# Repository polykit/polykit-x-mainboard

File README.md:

# Polykit X8 Mainboard

_THIS IS NOT A FINISHED PRODUCT IN ANY WAY AND STILL UNDER HEAVY DEVELOPMENT - USE AT YOUR OWN RISK!_

This repository contains Kicad schematics and PCB layout for a main board for a polyphonic synthesizer that is controlled by a micro controller.

Key features:

* 8 voice cards
* 16-bit DAC
* Atmel2560 micro controller
* Eurorack powered
* MIDI input/output

All parameters of the voice cards are controlled by the DAC. That means patches can be stored and recalled.

There is a video playlist on the design process https://makertube.net/w/p/3N2fRjXwT2SfAUv2VkMy3e

Related repositories:

* Voice Card: https://github.com/polykit/polykit-x-voice-card
* Control Board: https://github.com/polykit/polykit-x-controlboard
* Input Board: _soon_
* Software: _soon_
* Power Supply: https://github.com/polykit/eurorack-psu

## BOM

|Reference                                                    |Value           |Footprint                                                     |Qty|
|-------------------------------------------------------------|----------------|--------------------------------------------------------------|---|
|C1, C2, C11-C18, C23-C25, C31-C34, C43-C47, C56-C59, C64, C65|100n ceramic    |Capacitor_SMD:C_1206_3216Metric_Pad1.33x1.80mm_HandSolder     |28 |
|C3-C10, C19-C22, C26-C29, C35-C42, C48-C55                   |10n film, PPS   |Capacitor_SMD:C_1206_3216Metric_Pad1.33x1.80mm_HandSolder     |32 |
|C30                                                          |10u             |Capacitor_SMD:CP_Elec_5x5.9                                   |1  |
|C60-C63                                                      |100u            |Capacitor_SMD:CP_Elec_6.3x7.7                                 |4  |
|D1                                                           |1N4148WS        |Diode_SMD:D_SOD-323_HandSoldering                             |1  |
|J1                                                           |POWER           |Connector_IDC:IDC-Header_2x08_P2.54mm_Vertical                |1  |
|J2                                                           |OUTPUT          |Connector_Molex:Molex_KK-254_AE-6410-03A_1x03_P2.54mm_Vertical|1  |
|J3                                                           |MIDI IN         |Connector_Molex:Molex_KK-254_AE-6410-02A_1x02_P2.54mm_Vertical|1  |
|J4                                                           |MIDI_OUT        |Connector_Molex:Molex_KK-254_AE-6410-02A_1x02_P2.54mm_Vertical|1  |
|J5                                                           |EXTERNAL_IN     |Connector_Molex:Molex_KK-254_AE-6410-02A_1x02_P2.54mm_Vertical|1  |
|J6                                                           |I2C_1           |Connector_IDC:IDC-Header_2x05_P2.54mm_Vertical                |1  |
|J7                                                           |I2C_2           |Connector_IDC:IDC-Header_2x05_P2.54mm_Vertical                |1  |
|J8                                                           |SPI             |Connector_IDC:IDC-Header_2x05_P2.54mm_Vertical                |1  |
|J9                                                           |EXT_ANALOG      |Connector_IDC:IDC-Header_2x08_P2.54mm_Vertical                |1  |
|J10                                                          |EXT_DIGITAL     |Connector_IDC:IDC-Header_2x05_P2.54mm_Vertical                |1  |
|R1-R7, R13-R41                                               |100k            |Resistor_SMD:R_1206_3216Metric_Pad1.30x1.75mm_HandSolder      |36 |
|R8, R42, R43                                                 |1k              |Resistor_SMD:R_1206_3216Metric_Pad1.30x1.75mm_HandSolder      |3  |
|R9-R12, R47                                                  |10k             |Resistor_SMD:R_1206_3216Metric_Pad1.30x1.75mm_HandSolder      |5  |
|R44-R46                                                      |220R            |Resistor_SMD:R_1206_3216Metric_Pad1.30x1.75mm_HandSolder      |3  |
|U1                                                           |Mega2560Pro_Mini|aga:Mega2560Pro_Embed_RobotDyn                                |1  |
|U2, U5, U12, U15                                             |CD4051B         |Package_SO:SO-16_5.3x10.2mm_P1.27mm                           |4  |
|U3, U4, U6-U8, U13, U14, U16, U17, U19                       |TL074           |Package_SO:SO-14_3.9x8.65mm_P1.27mm                           |10 |
|U9                                                           |LM4040AIM3-5.0  |Package_TO_SOT_SMD:SOT-23                                     |1  |
|U10                                                          |AD5676ARUZ      |Package_SO:TSSOP-20_4.4x6.5mm_P0.65mm                         |1  |
|U11                                                          |TL072           |Package_SO:SO-8_3.9x4.9mm_P1.27mm                             |1  |
|U18                                                          |L7905           |Package_TO_SOT_SMD:TO-263-2                                   |1  |
|U20                                                          |6N137           |Package_DIP:DIP-8_W7.62mm_SMDSocket_SmallPads                 |1  |
|VOICE1-VOICE8                                                |VOICE           |Connector_PinSocket_2.54mm:PinSocket_1x36_P2.54mm_Vertical    |8  |

## Tweaks

* If saw/triangle signal is not audible replace R38 with a 220k resistor on the voice cards

## References

https://www.analog.com/media/en/technical-documentation/data-sheets/ad5676.pdf

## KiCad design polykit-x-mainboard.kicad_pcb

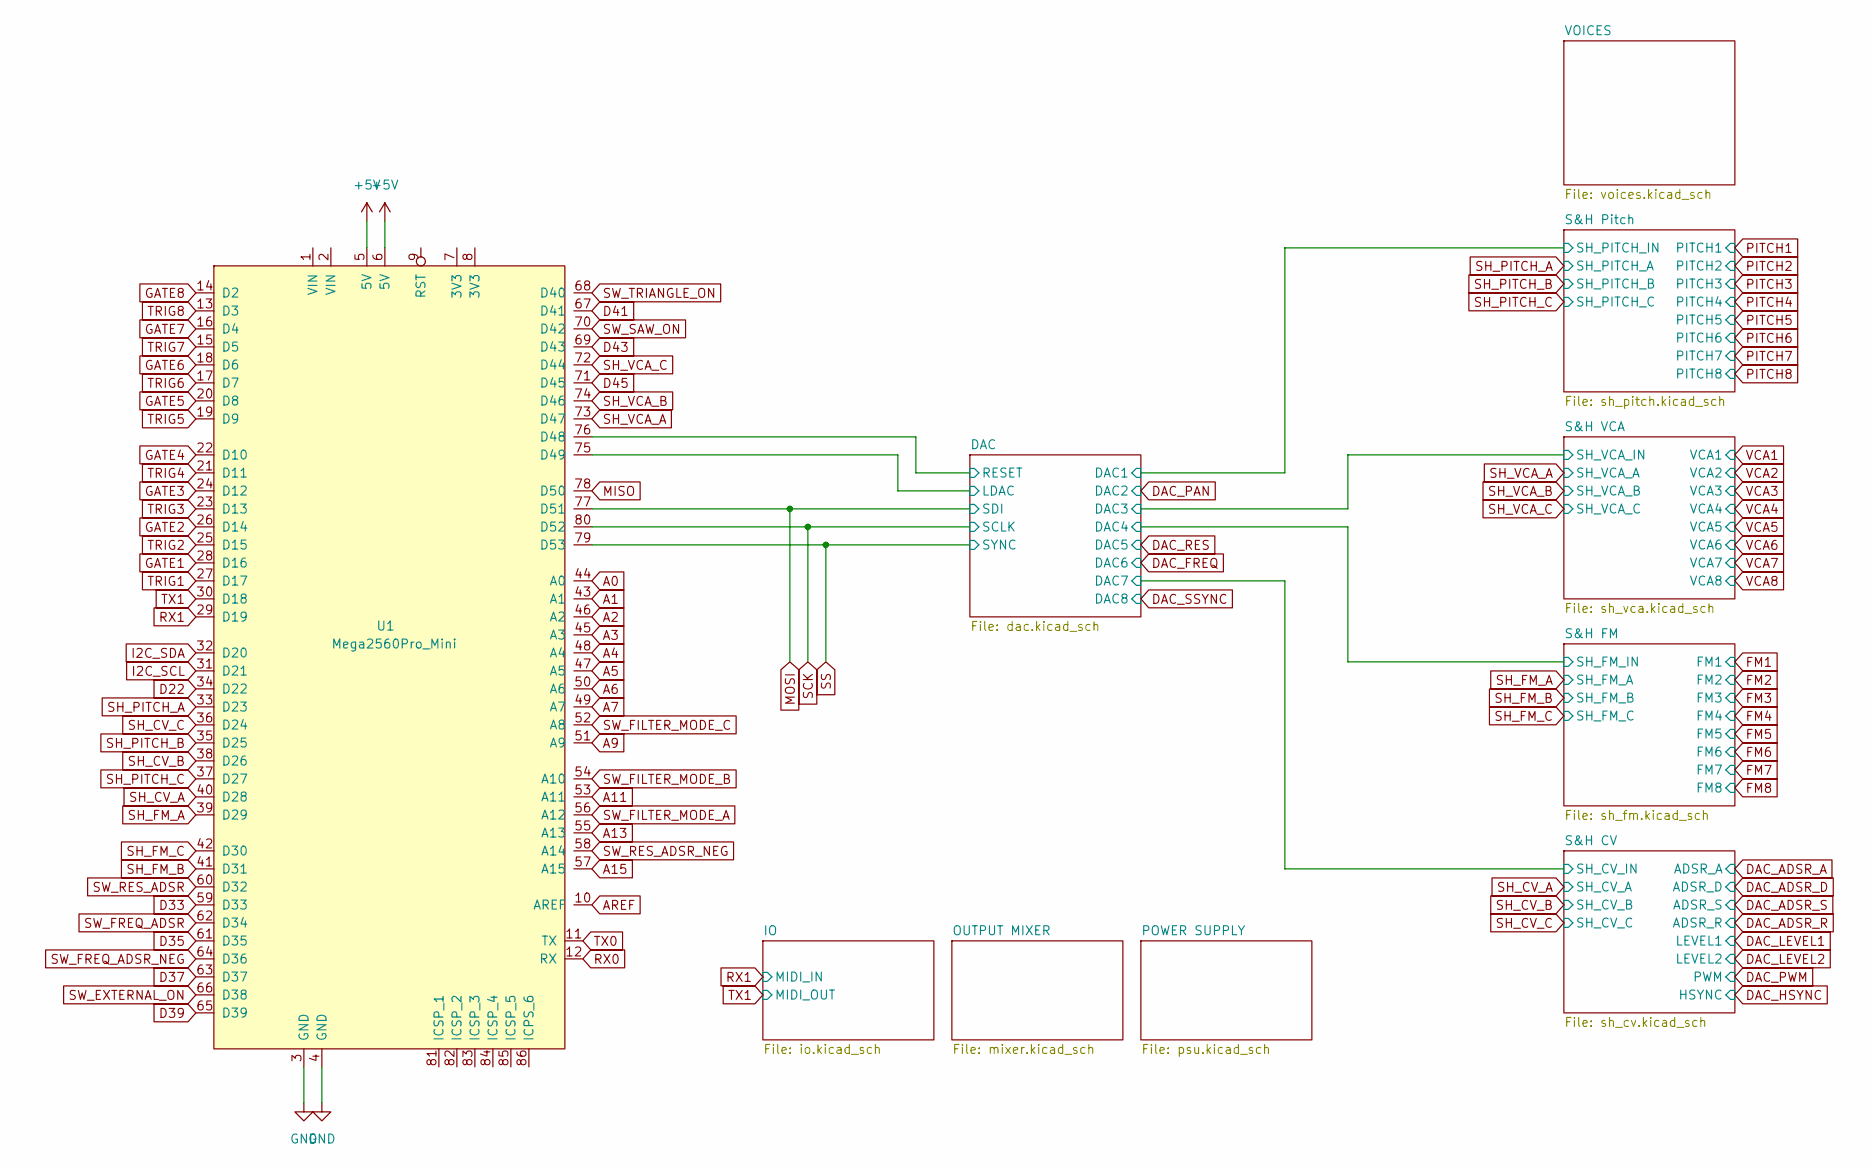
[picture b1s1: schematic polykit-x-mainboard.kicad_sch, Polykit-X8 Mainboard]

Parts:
U1: Mega2560Pro_Mini; Mega2560Pro_Embed_RobotDyn

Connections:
+5V: U1.5 (5V), U1.6 (5V); also elsewhere on the board
/DAC/LDAC: U1.75 (D49); also elsewhere on the board
/DAC/RESET: U1.76 (D48); also elsewhere on the board
A0: U1.44 (A0); also elsewhere on the board
A1: U1.43 (A1); also elsewhere on the board
A2: U1.46 (A2); also elsewhere on the board
A3: U1.45 (A3); also elsewhere on the board
A4: U1.48 (A4); also elsewhere on the board
A5: U1.47 (A5); also elsewhere on the board
A6: U1.50 (A6); also elsewhere on the board
A7: U1.49 (A7); also elsewhere on the board
A9: U1.51 (A9); also elsewhere on the board
A11: U1.53 (A11); also elsewhere on the board
A13: U1.55 (A13); also elsewhere on the board
A15: U1.57 (A15); also elsewhere on the board
AREF: U1.10 (AREF); also elsewhere on the board
D22: U1.34 (D22); also elsewhere on the board
D33: U1.59 (D33); also elsewhere on the board
D35: U1.61 (D35); also elsewhere on the board
D37: U1.63 (D37); also elsewhere on the board
D39: U1.65 (D39); also elsewhere on the board
D41: U1.67 (D41); also elsewhere on the board
D43: U1.69 (D43); also elsewhere on the board
D45: U1.71 (D45); also elsewhere on the board
GATE1: U1.28 (D16); also elsewhere on the board
GATE2: U1.26 (D14); also elsewhere on the board
GATE3: U1.24 (D12); also elsewhere on the board
GATE4: U1.22 (D10); also elsewhere on the board
GATE5: U1.20 (D8); also elsewhere on the board
GATE6: U1.18 (D6); also elsewhere on the board
GATE7: U1.16 (D4); also elsewhere on the board
GATE8: U1.14 (D2); also elsewhere on the board
GND: U1.3 (GND), U1.4 (GND); also elsewhere on the board
I2C_SCL: U1.31 (D21); also elsewhere on the board
I2C_SDA: U1.32 (D20); also elsewhere on the board
MISO: U1.78 (D50); also elsewhere on the board
MOSI: U1.77 (D51); also elsewhere on the board
RX0: U1.12 (RX); also elsewhere on the board
RX1: U1.29 (D19); also elsewhere on the board
SCK: U1.80 (D52); also elsewhere on the board
SH_CV_A: U1.40 (D28); also elsewhere on the board
SH_CV_B: U1.38 (D26); also elsewhere on the board
SH_CV_C: U1.36 (D24); also elsewhere on the board
SH_FM_A: U1.39 (D29); also elsewhere on the board
SH_FM_B: U1.41 (D31); also elsewhere on the board
SH_FM_C: U1.42 (D30); also elsewhere on the board
SH_PITCH_A: U1.33 (D23); also elsewhere on the board
SH_PITCH_B: U1.35 (D25); also elsewhere on the board
SH_PITCH_C: U1.37 (D27); also elsewhere on the board
SH_VCA_A: U1.73 (D47); also elsewhere on the board
SH_VCA_B: U1.74 (D46); also elsewhere on the board
SH_VCA_C: U1.72 (D44); also elsewhere on the board
SS: U1.79 (D53); also elsewhere on the board
SW_EXTERNAL_ON: U1.66 (D38); also elsewhere on the board
SW_FILTER_MODE_A: U1.56 (A12); also elsewhere on the board
SW_FILTER_MODE_B: U1.54 (A10); also elsewhere on the board
SW_FILTER_MODE_C: U1.52 (A8); also elsewhere on the board
SW_FREQ_ADSR: U1.62 (D34); also elsewhere on the board
SW_FREQ_ADSR_NEG: U1.64 (D36); also elsewhere on the board
SW_RES_ADSR: U1.60 (D32); also elsewhere on the board
SW_RES_ADSR_NEG: U1.58 (A14); also elsewhere on the board
SW_SAW_ON: U1.70 (D42); also elsewhere on the board
SW_TRIANGLE_ON: U1.68 (D40); also elsewhere on the board
TRIG1: U1.27 (D17); also elsewhere on the board
TRIG2: U1.25 (D15); also elsewhere on the board
TRIG3: U1.23 (D13); also elsewhere on the board
TRIG4: U1.21 (D11); also elsewhere on the board
TRIG5: U1.19 (D9); also elsewhere on the board
TRIG6: U1.17 (D7); also elsewhere on the board
TRIG7: U1.15 (D5); also elsewhere on the board
TRIG8: U1.13 (D3); also elsewhere on the board
TX0: U1.11 (TX); also elsewhere on the board
TX1: U1.30 (D18); also elsewhere on the board

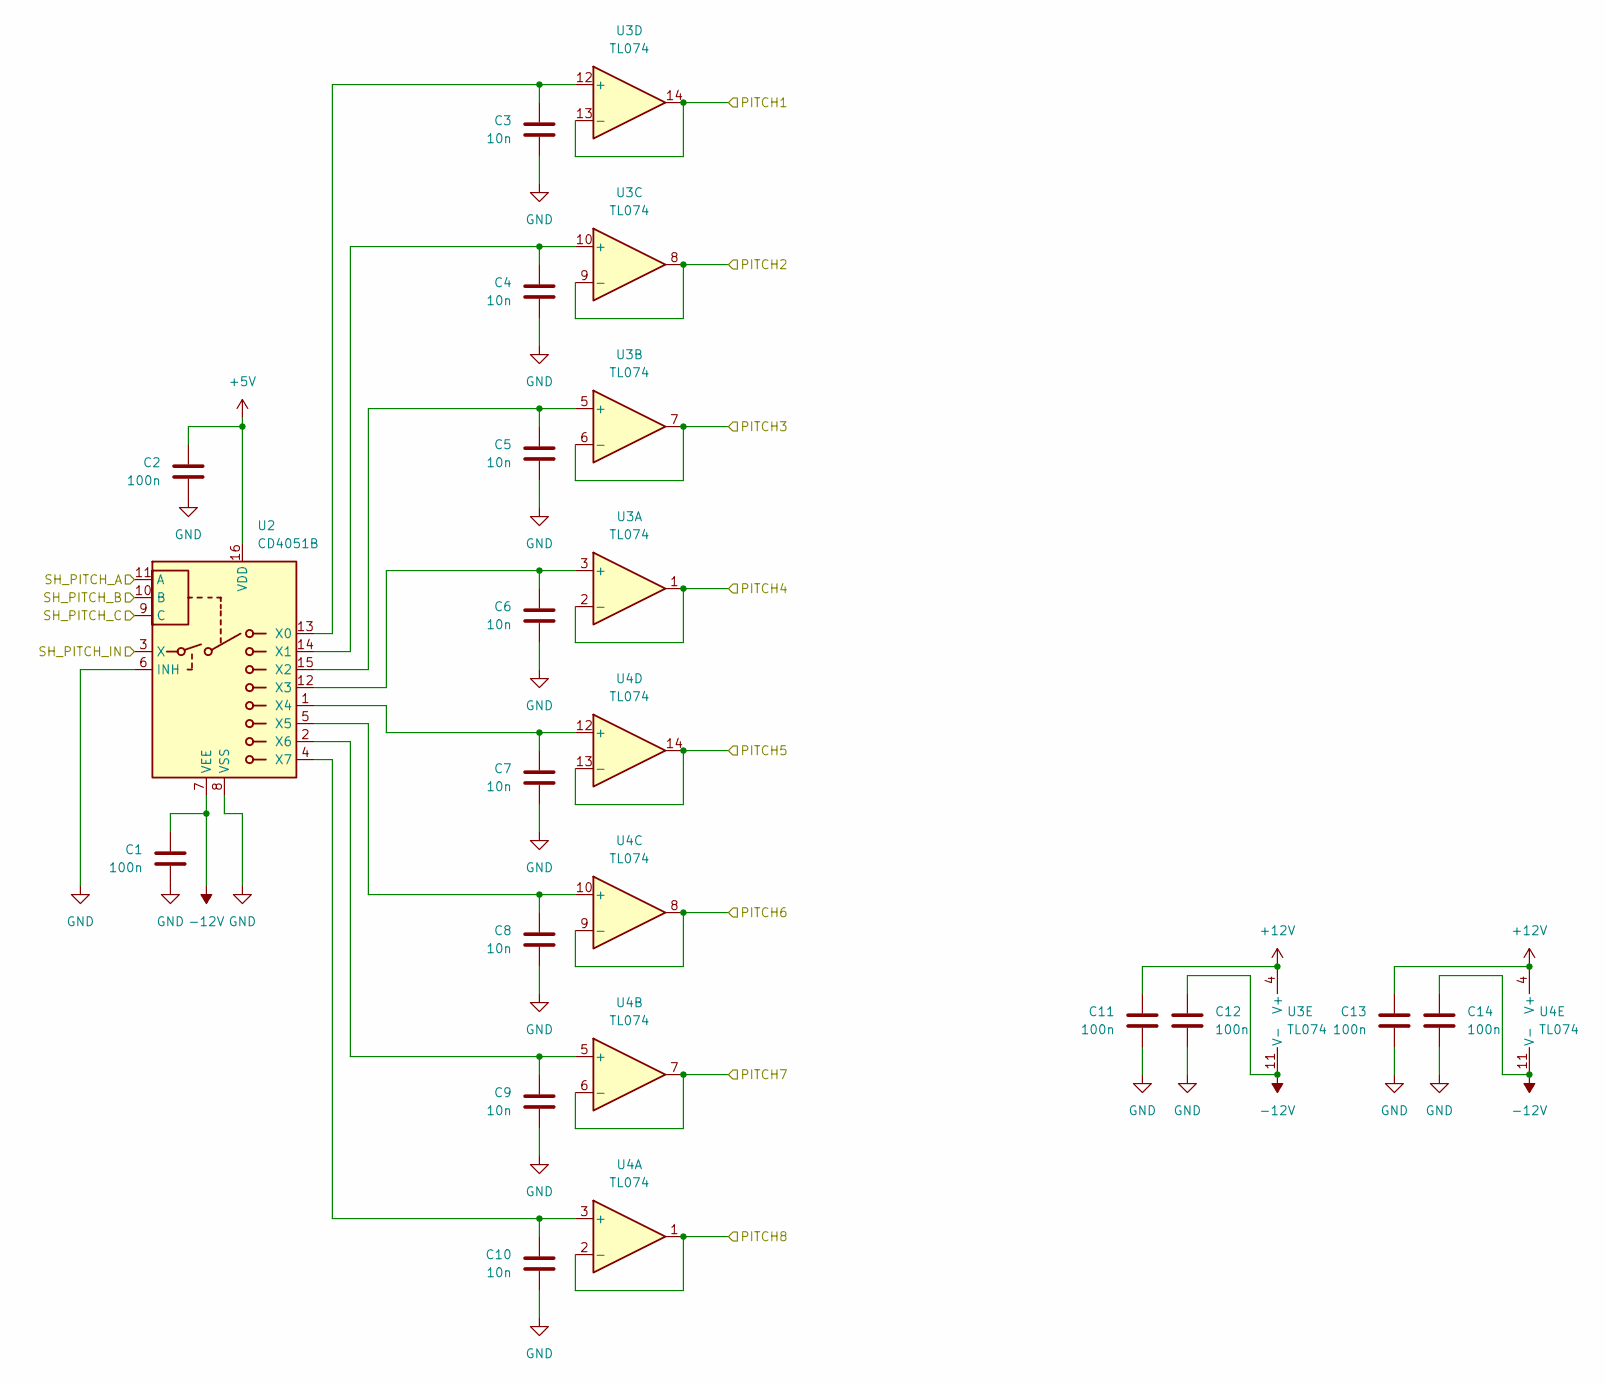
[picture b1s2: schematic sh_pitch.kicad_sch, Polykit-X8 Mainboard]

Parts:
C1, C2, C11, C12, C13, C14: 100n; C_1206_3216Metric_Pad1.33x1.80mm_HandSolder
C3, C4, C5, C6, C7, C8, C9, C10: 10n; C_1206_3216Metric_Pad1.33x1.80mm_HandSolder
U2: CD4051B; SO-16_5.3x10.2mm_P1.27mm
U3, U4: TL074; SO-14_3.9x8.65mm_P1.27mm

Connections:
+5V: C2.1, U2.16 (VDD); also elsewhere on the board
+12V: C11.1, C13.1, U3.4 (V+), U4.4 (V+); also elsewhere on the board
-12V: C1.1, C12.1, C14.1, U2.7 (VEE), U3.11 (V-), U4.11 (V-); also elsewhere on the board
/DAC/DAC1: U2.3 (X); also elsewhere on the board
GND: C1.2, C2.2, C3.2, C4.2, C5.2, C6.2, C7.2, C8.2, C9.2, C10.2, C11.2, C12.2, C13.2, C14.2, U2.6 (INH), U2.8 (VSS); also elsewhere on the board
unnamed: C3.1, U2.13 (X0), U3.12 (+)
unnamed: C4.1, U2.14 (X1), U3.10 (+)
unnamed: C5.1, U2.15 (X2), U3.5 (+)
unnamed: C6.1, U2.12 (X3), U3.3 (+)
unnamed: C7.1, U2.1 (X4), U4.12 (+)
unnamed: C8.1, U2.5 (X5), U4.10 (+)
unnamed: C9.1, U2.2 (X6), U4.5 (+)
unnamed: C10.1, U2.4 (X7), U4.3 (+)
PITCH1: U3.13 (-), U3.14; also elsewhere on the board
PITCH2: U3.8, U3.9 (-); also elsewhere on the board
PITCH3: U3.6 (-), U3.7; also elsewhere on the board
PITCH4: U3.1, U3.2 (-); also elsewhere on the board
PITCH5: U4.13 (-), U4.14; also elsewhere on the board
PITCH6: U4.8, U4.9 (-); also elsewhere on the board
PITCH7: U4.6 (-), U4.7; also elsewhere on the board
PITCH8: U4.1, U4.2 (-); also elsewhere on the board
SH_PITCH_A: U2.11 (A); also elsewhere on the board
SH_PITCH_B: U2.10 (B); also elsewhere on the board
SH_PITCH_C: U2.9 (C); also elsewhere on the board

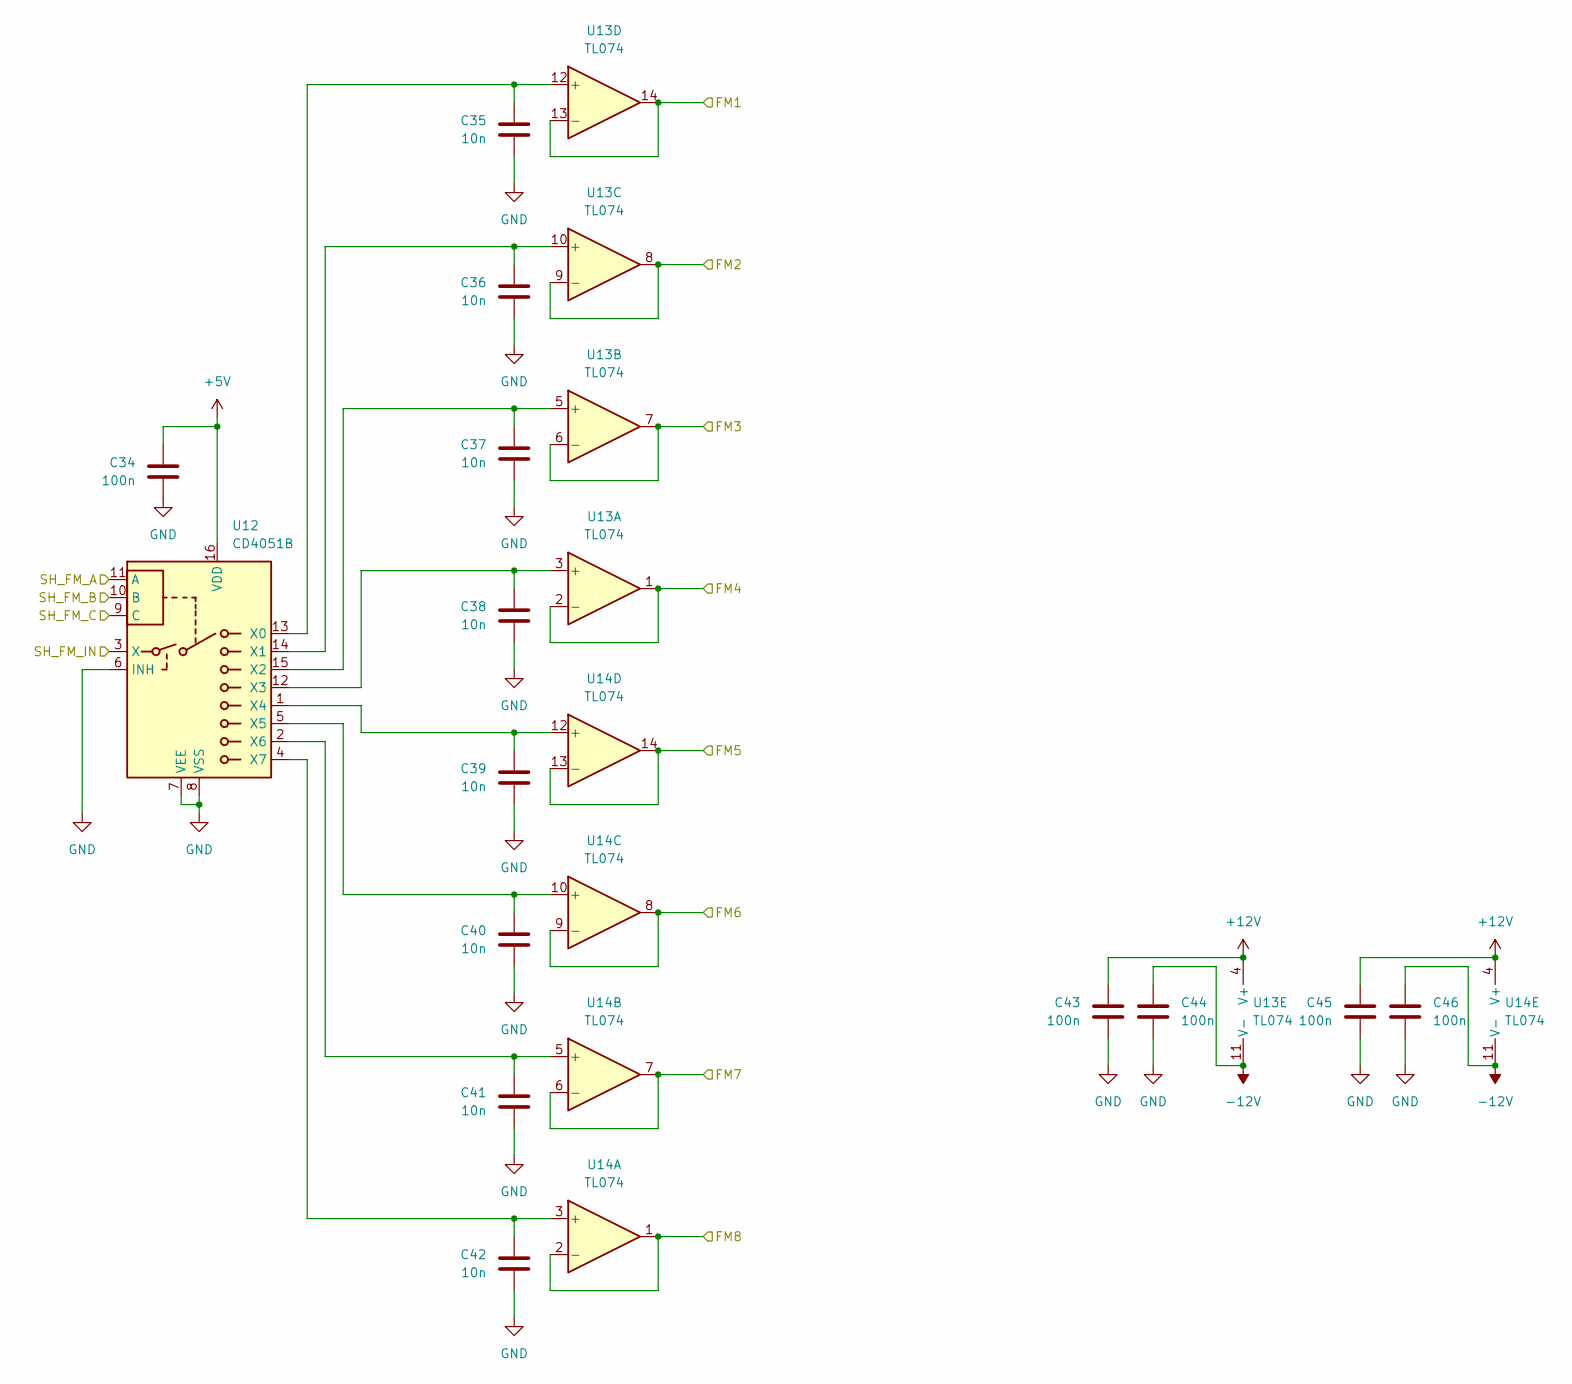
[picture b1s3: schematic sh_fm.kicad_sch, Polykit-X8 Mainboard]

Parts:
C34, C43, C44, C45, C46: 100n; C_1206_3216Metric_Pad1.33x1.80mm_HandSolder
C35, C36, C37, C38, C39, C40, C41, C42: 10n; C_1206_3216Metric_Pad1.33x1.80mm_HandSolder
U12: CD4051B; SO-16_5.3x10.2mm_P1.27mm
U13, U14: TL074; SO-14_3.9x8.65mm_P1.27mm

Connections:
+5V: C34.1, U12.16 (VDD); also elsewhere on the board
+12V: C43.1, C45.1, U13.4 (V+), U14.4 (V+); also elsewhere on the board
-12V: C44.1, C46.1, U13.11 (V-), U14.11 (V-); also elsewhere on the board
/DAC/DAC4: U12.3 (X); also elsewhere on the board
FM1: U13.13 (-), U13.14; also elsewhere on the board
FM2: U13.8, U13.9 (-); also elsewhere on the board
FM3: U13.6 (-), U13.7; also elsewhere on the board
FM4: U13.1, U13.2 (-); also elsewhere on the board
FM5: U14.13 (-), U14.14; also elsewhere on the board
FM6: U14.8, U14.9 (-); also elsewhere on the board
FM7: U14.6 (-), U14.7; also elsewhere on the board
FM8: U14.1, U14.2 (-); also elsewhere on the board
GND: C34.2, C35.2, C36.2, C37.2, C38.2, C39.2, C40.2, C41.2, C42.2, C43.2, C44.2, C45.2, C46.2, U12.6 (INH), U12.7 (VEE), U12.8 (VSS); also elsewhere on the board
unnamed: C35.1, U12.13 (X0), U13.12 (+)
unnamed: C36.1, U12.14 (X1), U13.10 (+)
unnamed: C37.1, U12.15 (X2), U13.5 (+)
unnamed: C38.1, U12.12 (X3), U13.3 (+)
unnamed: C39.1, U12.1 (X4), U14.12 (+)
unnamed: C40.1, U12.5 (X5), U14.10 (+)
unnamed: C41.1, U12.2 (X6), U14.5 (+)
unnamed: C42.1, U12.4 (X7), U14.3 (+)
SH_FM_A: U12.11 (A); also elsewhere on the board
SH_FM_B: U12.10 (B); also elsewhere on the board
SH_FM_C: U12.9 (C); also elsewhere on the board

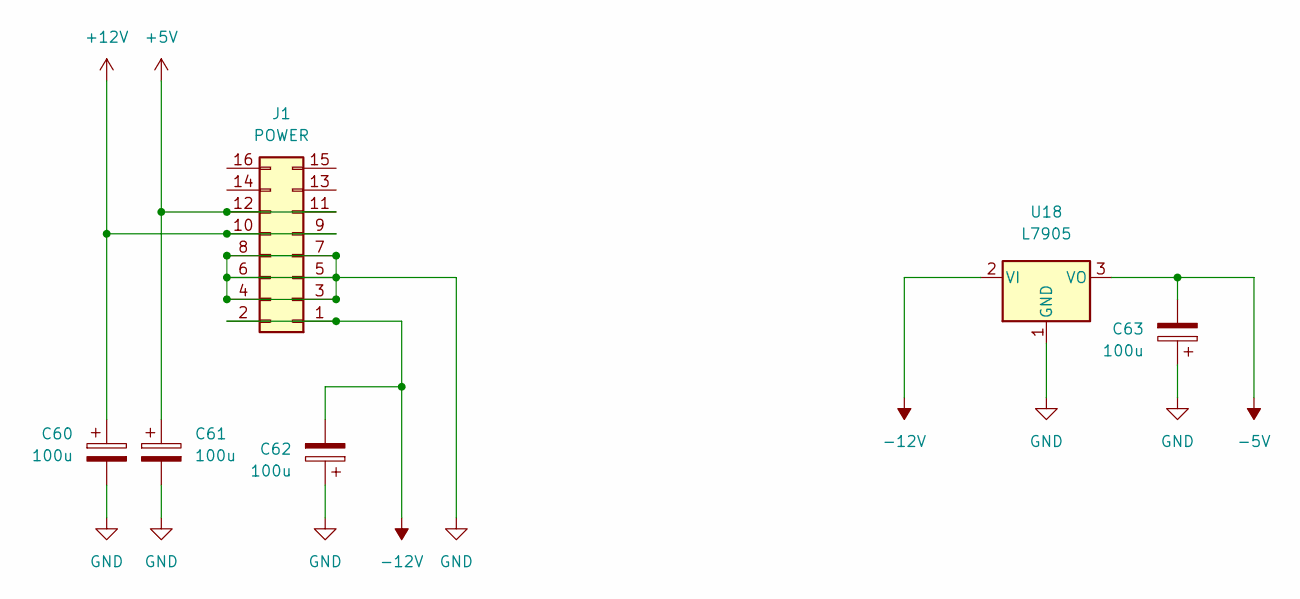
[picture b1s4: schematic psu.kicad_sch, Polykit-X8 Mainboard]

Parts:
C60, C61, C62, C63: 100u; CP_Elec_6.3x7.7
J1: POWER; IDC-Header_2x08_P2.54mm_Vertical
U18: L7905; TO-263-2

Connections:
+5V: C61.1, J1.11, J1.12; also elsewhere on the board
+12V: C60.1, J1.9, J1.10; also elsewhere on the board
-5V: C63.2, U18.3 (VO); also elsewhere on the board
-12V: C62.2, J1.1, J1.2, U18.2 (VI); also elsewhere on the board
GND: C60.2, C61.2, C62.1, C63.1, J1.3, J1.4, J1.5, J1.6, J1.7, J1.8, U18.1 (GND); also elsewhere on the board

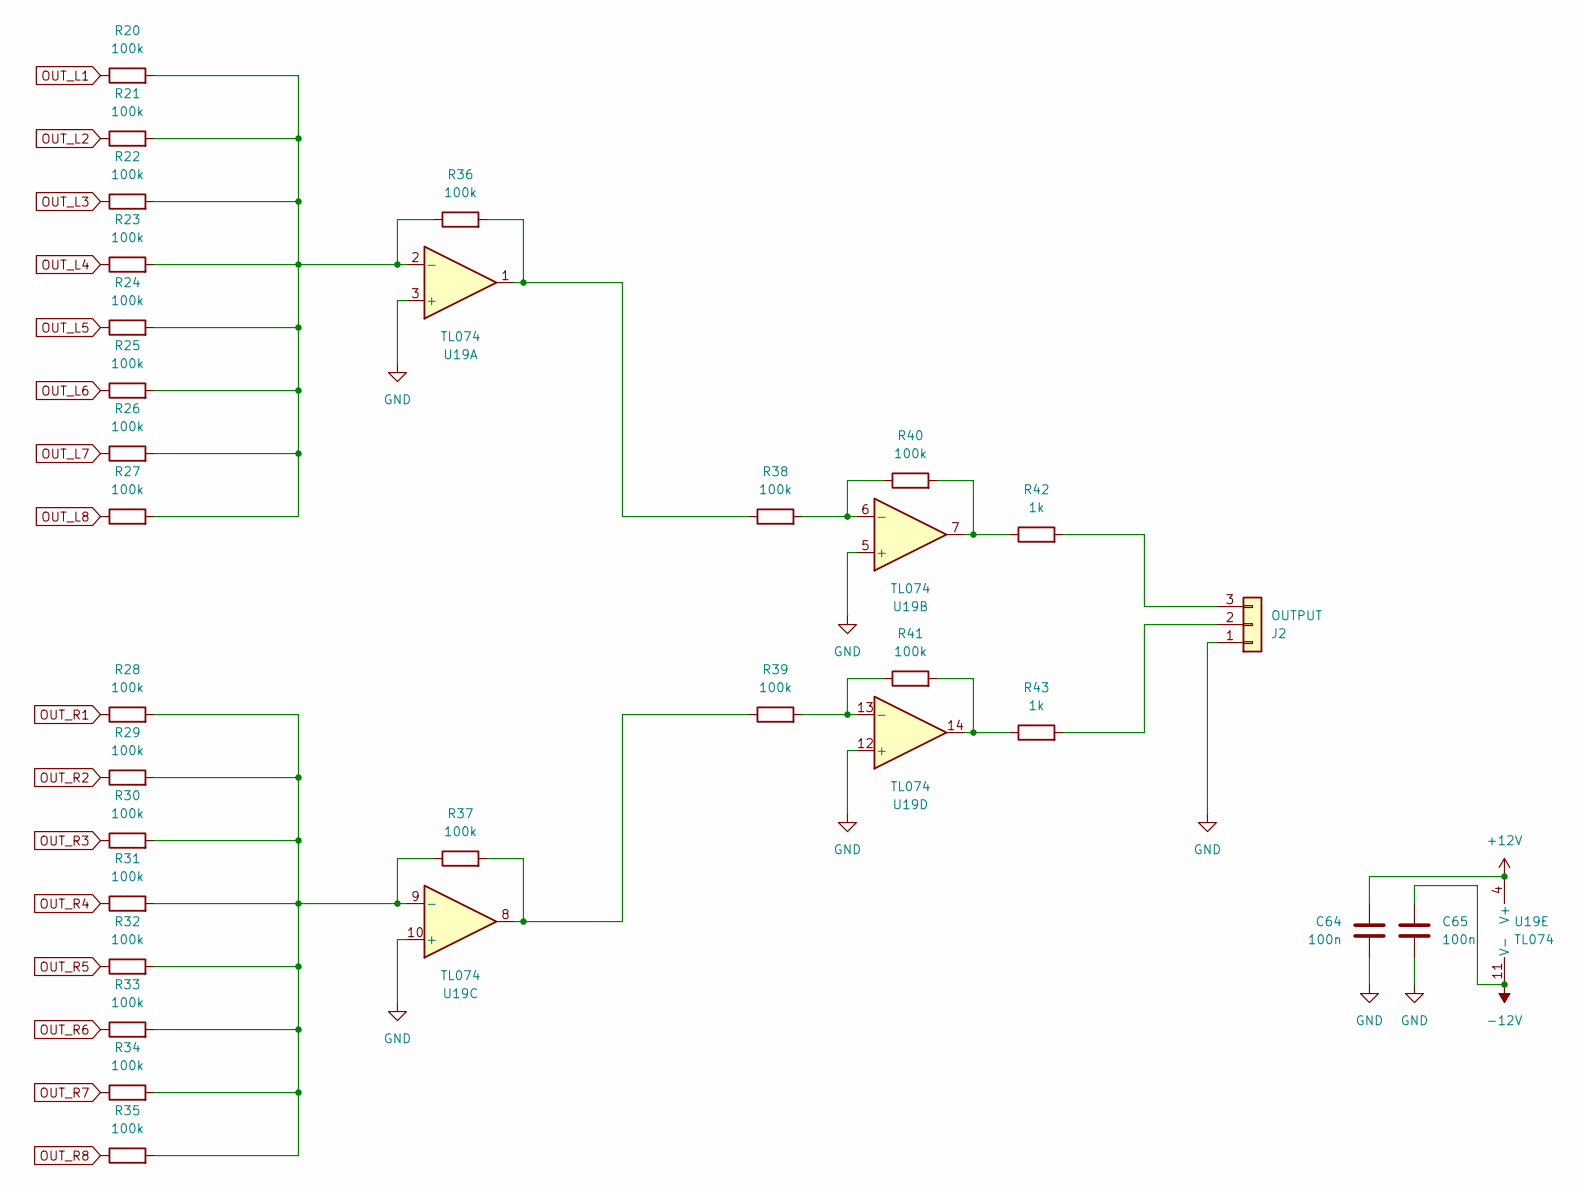
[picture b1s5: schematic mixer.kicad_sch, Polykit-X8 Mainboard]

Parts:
C64, C65: 100n; C_1206_3216Metric_Pad1.33x1.80mm_HandSolder
J2: OUTPUT; Molex_KK-254_AE-6410-03A_1x03_P2.54mm_Vertical
R20, R21, R22, R23, R24, R25, R26, R27, R28, R29, R30, R31, R32, R33, R34, R35, R36, R37, R38, R39, R40, R41: 100k; R_1206_3216Metric_Pad1.30x1.75mm_HandSolder
R42, R43: 1k; R_1206_3216Metric_Pad1.30x1.75mm_HandSolder
U19: TL074; SO-14_3.9x8.65mm_P1.27mm

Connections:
+12V: C64.1, U19.4 (V+); also elsewhere on the board
-12V: C65.1, U19.11 (V-); also elsewhere on the board
GND: C64.2, C65.2, J2.1, U19.3 (+), U19.5 (+), U19.10 (+), U19.12 (+); also elsewhere on the board
unnamed: J2.2, R43.2
unnamed: J2.3, R42.2
unnamed: R20.2, R21.2, R22.2, R23.2, R24.2, R25.2, R26.2, R27.2, R36.1, U19.2 (-)
unnamed: R28.2, R29.2, R30.2, R31.2, R32.2, R33.2, R34.2, R35.2, R37.1, U19.9 (-)
unnamed: R36.2, R38.1, U19.1
unnamed: R37.2, R39.1, U19.8
unnamed: R38.2, R40.1, U19.6 (-)
unnamed: R39.2, R41.1, U19.13 (-)
unnamed: R40.2, R42.1, U19.7
unnamed: R41.2, R43.1, U19.14
OUT_L1: R20.1; also elsewhere on the board
OUT_L2: R21.1; also elsewhere on the board
OUT_L3: R22.1; also elsewhere on the board
OUT_L4: R23.1; also elsewhere on the board
OUT_L5: R24.1; also elsewhere on the board
OUT_L6: R25.1; also elsewhere on the board
OUT_L7: R26.1; also elsewhere on the board
OUT_L8: R27.1; also elsewhere on the board
OUT_R1: R28.1; also elsewhere on the board
OUT_R2: R29.1; also elsewhere on the board
OUT_R3: R30.1; also elsewhere on the board
OUT_R4: R31.1; also elsewhere on the board
OUT_R5: R32.1; also elsewhere on the board
OUT_R6: R33.1; also elsewhere on the board
OUT_R7: R34.1; also elsewhere on the board
OUT_R8: R35.1; also elsewhere on the board

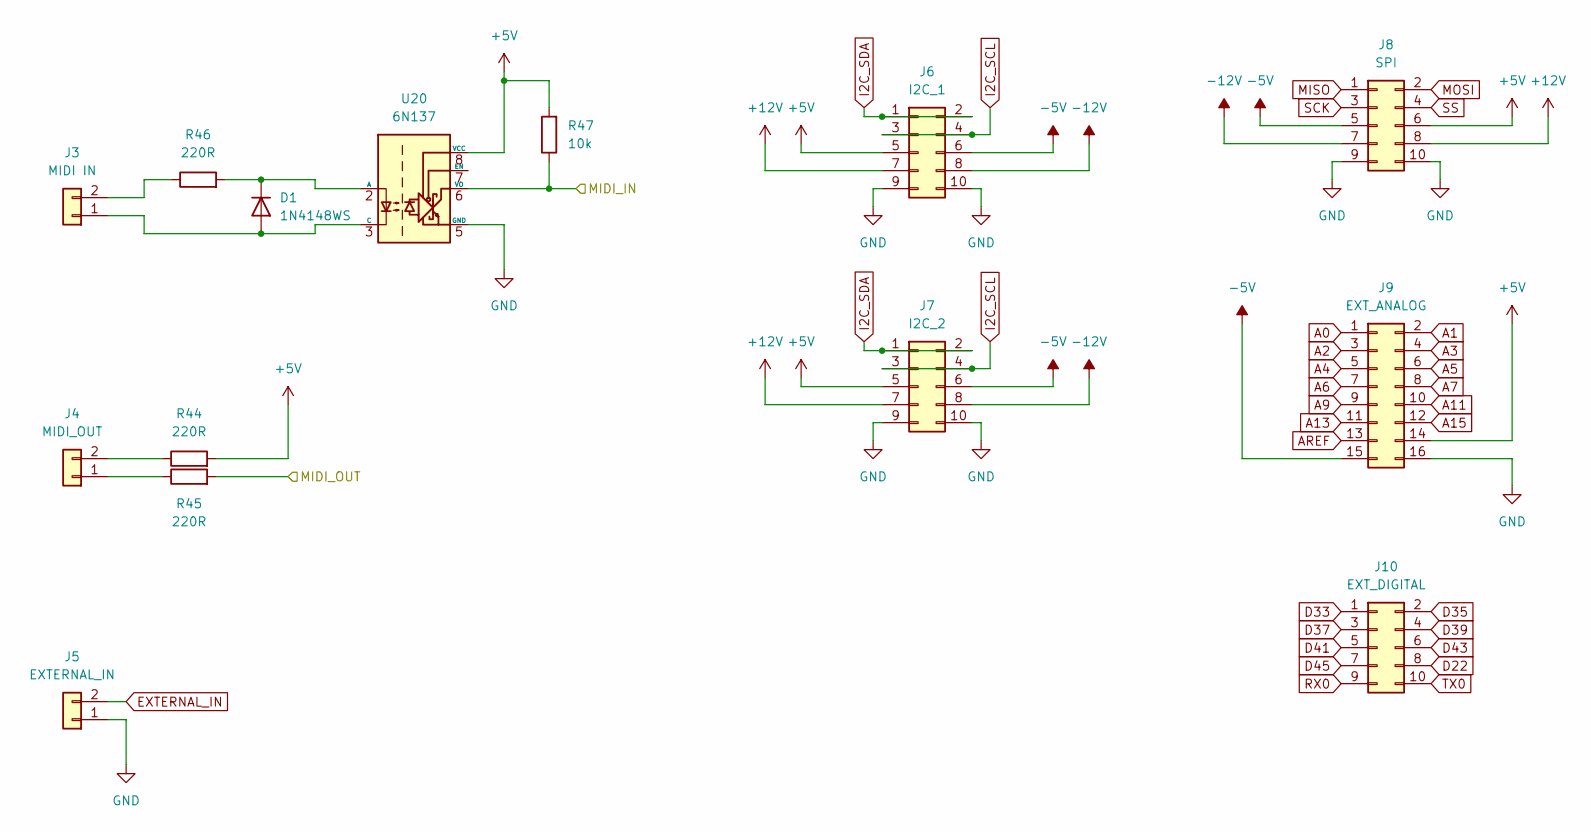
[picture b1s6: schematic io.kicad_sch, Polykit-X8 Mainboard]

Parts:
D1: 1N4148WS; D_SOD-323_HandSoldering
J3: MIDI IN; Molex_KK-254_AE-6410-02A_1x02_P2.54mm_Vertical
J4: MIDI_OUT; Molex_KK-254_AE-6410-02A_1x02_P2.54mm_Vertical
J5: EXTERNAL_IN; Molex_KK-254_AE-6410-02A_1x02_P2.54mm_Vertical
J6: I2C_1; IDC-Header_2x05_P2.54mm_Vertical
J7: I2C_2; IDC-Header_2x05_P2.54mm_Vertical
J8: SPI; IDC-Header_2x05_P2.54mm_Vertical
J9: EXT_ANALOG; IDC-Header_2x08_P2.54mm_Vertical
J10: EXT_DIGITAL; IDC-Header_2x05_P2.54mm_Vertical
R44, R45, R46: 220R; R_1206_3216Metric_Pad1.30x1.75mm_HandSolder
R47: 10k; R_1206_3216Metric_Pad1.30x1.75mm_HandSolder
U20: 6N137; DIP-8_W7.62mm_SMDSocket_SmallPads

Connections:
+5V: J6.5, J7.5, J8.6, J9.14, R44.2, R47.2, U20.8 (VCC); also elsewhere on the board
+12V: J6.7, J7.7, J8.8; also elsewhere on the board
-5V: J6.6, J7.6, J8.5, J9.15; also elsewhere on the board
-12V: J6.8, J7.8, J8.7; also elsewhere on the board
A0: J9.1; also elsewhere on the board
A1: J9.2; also elsewhere on the board
A2: J9.3; also elsewhere on the board
A3: J9.4; also elsewhere on the board
A4: J9.5; also elsewhere on the board
A5: J9.6; also elsewhere on the board
A6: J9.7; also elsewhere on the board
A7: J9.8; also elsewhere on the board
A9: J9.9; also elsewhere on the board
A11: J9.10; also elsewhere on the board
A13: J9.11; also elsewhere on the board
A15: J9.12; also elsewhere on the board
AREF: J9.13; also elsewhere on the board
D22: J10.8; also elsewhere on the board
D33: J10.1; also elsewhere on the board
D35: J10.2; also elsewhere on the board
D37: J10.3; also elsewhere on the board
D39: J10.4; also elsewhere on the board
D41: J10.5; also elsewhere on the board
D43: J10.6; also elsewhere on the board
D45: J10.7; also elsewhere on the board
EXTERNAL_IN: J5.2; also elsewhere on the board
GND: J5.1, J6.9, J6.10, J7.9, J7.10, J8.9, J8.10, J9.16, U20.5 (GND); also elsewhere on the board
I2C_SCL: J6.3, J6.4, J7.3, J7.4; also elsewhere on the board
I2C_SDA: J6.1, J6.2, J7.1, J7.2; also elsewhere on the board
MISO: J8.1; also elsewhere on the board
MOSI: J8.2; also elsewhere on the board
unnamed: D1.1 (K), R46.2, U20.2 (A)
unnamed: D1.2 (A), J3.1, U20.3 (C)
unnamed: J3.2, R46.1
unnamed: J4.1, R45.1
unnamed: J4.2, R44.1
RX0: J10.9; also elsewhere on the board
RX1: R47.1, U20.6 (VO); also elsewhere on the board
SCK: J8.3; also elsewhere on the board
SS: J8.4; also elsewhere on the board
TX0: J10.10; also elsewhere on the board
TX1: R45.2; also elsewhere on the board

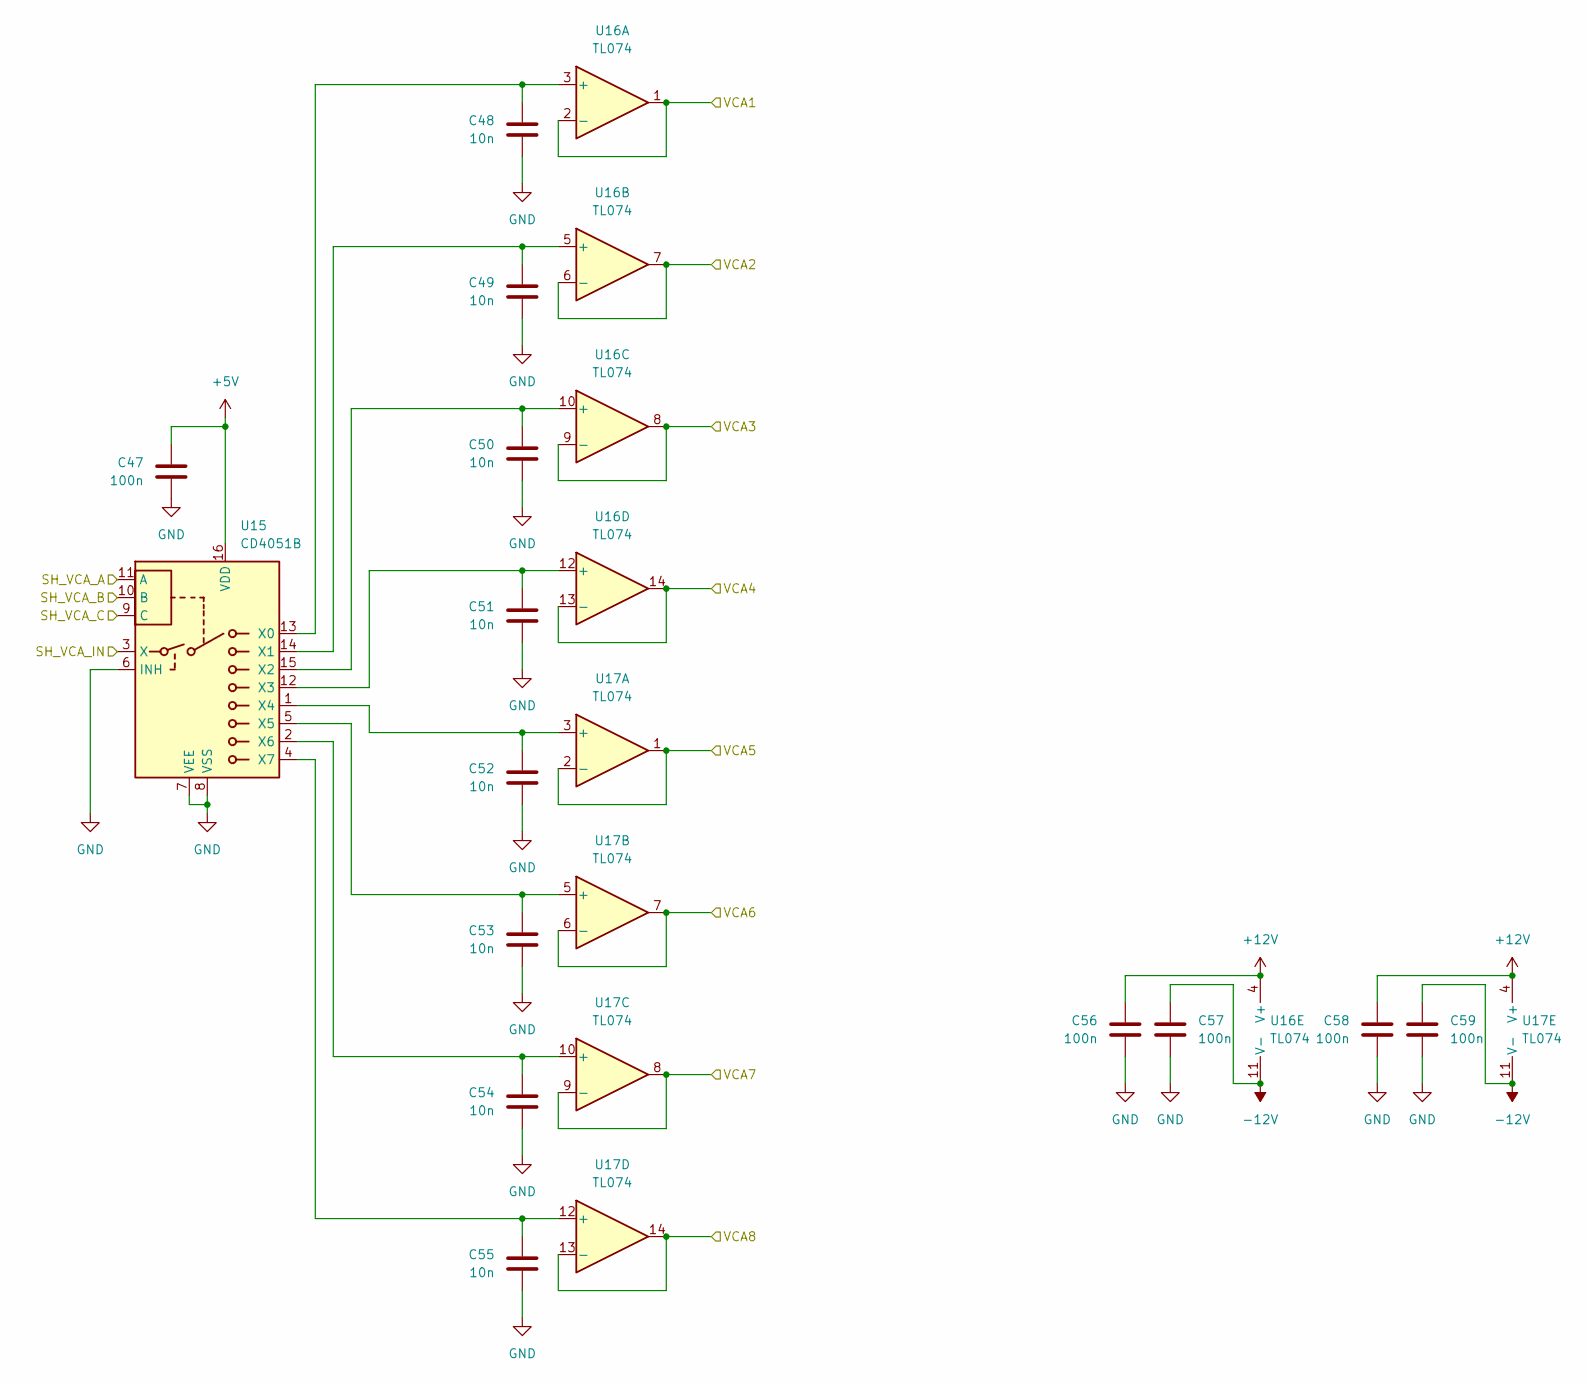
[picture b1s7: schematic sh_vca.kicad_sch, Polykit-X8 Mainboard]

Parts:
C47, C56, C57, C58, C59: 100n; C_1206_3216Metric_Pad1.33x1.80mm_HandSolder
C48, C49, C50, C51, C52, C53, C54, C55: 10n; C_1206_3216Metric_Pad1.33x1.80mm_HandSolder
U15: CD4051B; SO-16_5.3x10.2mm_P1.27mm
U16, U17: TL074; SO-14_3.9x8.65mm_P1.27mm

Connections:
+5V: C47.1, U15.16 (VDD); also elsewhere on the board
+12V: C56.1, C58.1, U16.4 (V+), U17.4 (V+); also elsewhere on the board
-12V: C57.1, C59.1, U16.11 (V-), U17.11 (V-); also elsewhere on the board
/DAC/DAC3: U15.3 (X); also elsewhere on the board
GND: C47.2, C48.2, C49.2, C50.2, C51.2, C52.2, C53.2, C54.2, C55.2, C56.2, C57.2, C58.2, C59.2, U15.6 (INH), U15.7 (VEE), U15.8 (VSS); also elsewhere on the board
unnamed: C48.1, U15.13 (X0), U16.3 (+)
unnamed: C49.1, U15.14 (X1), U16.5 (+)
unnamed: C50.1, U15.15 (X2), U16.10 (+)
unnamed: C51.1, U15.12 (X3), U16.12 (+)
unnamed: C52.1, U15.1 (X4), U17.3 (+)
unnamed: C53.1, U15.5 (X5), U17.5 (+)
unnamed: C54.1, U15.2 (X6), U17.10 (+)
unnamed: C55.1, U15.4 (X7), U17.12 (+)
SH_VCA_A: U15.11 (A); also elsewhere on the board
SH_VCA_B: U15.10 (B); also elsewhere on the board
SH_VCA_C: U15.9 (C); also elsewhere on the board
VCA1: U16.1, U16.2 (-); also elsewhere on the board
VCA2: U16.6 (-), U16.7; also elsewhere on the board
VCA3: U16.8, U16.9 (-); also elsewhere on the board
VCA4: U16.13 (-), U16.14; also elsewhere on the board
VCA5: U17.1, U17.2 (-); also elsewhere on the board
VCA6: U17.6 (-), U17.7; also elsewhere on the board
VCA7: U17.8, U17.9 (-); also elsewhere on the board
VCA8: U17.13 (-), U17.14; also elsewhere on the board
